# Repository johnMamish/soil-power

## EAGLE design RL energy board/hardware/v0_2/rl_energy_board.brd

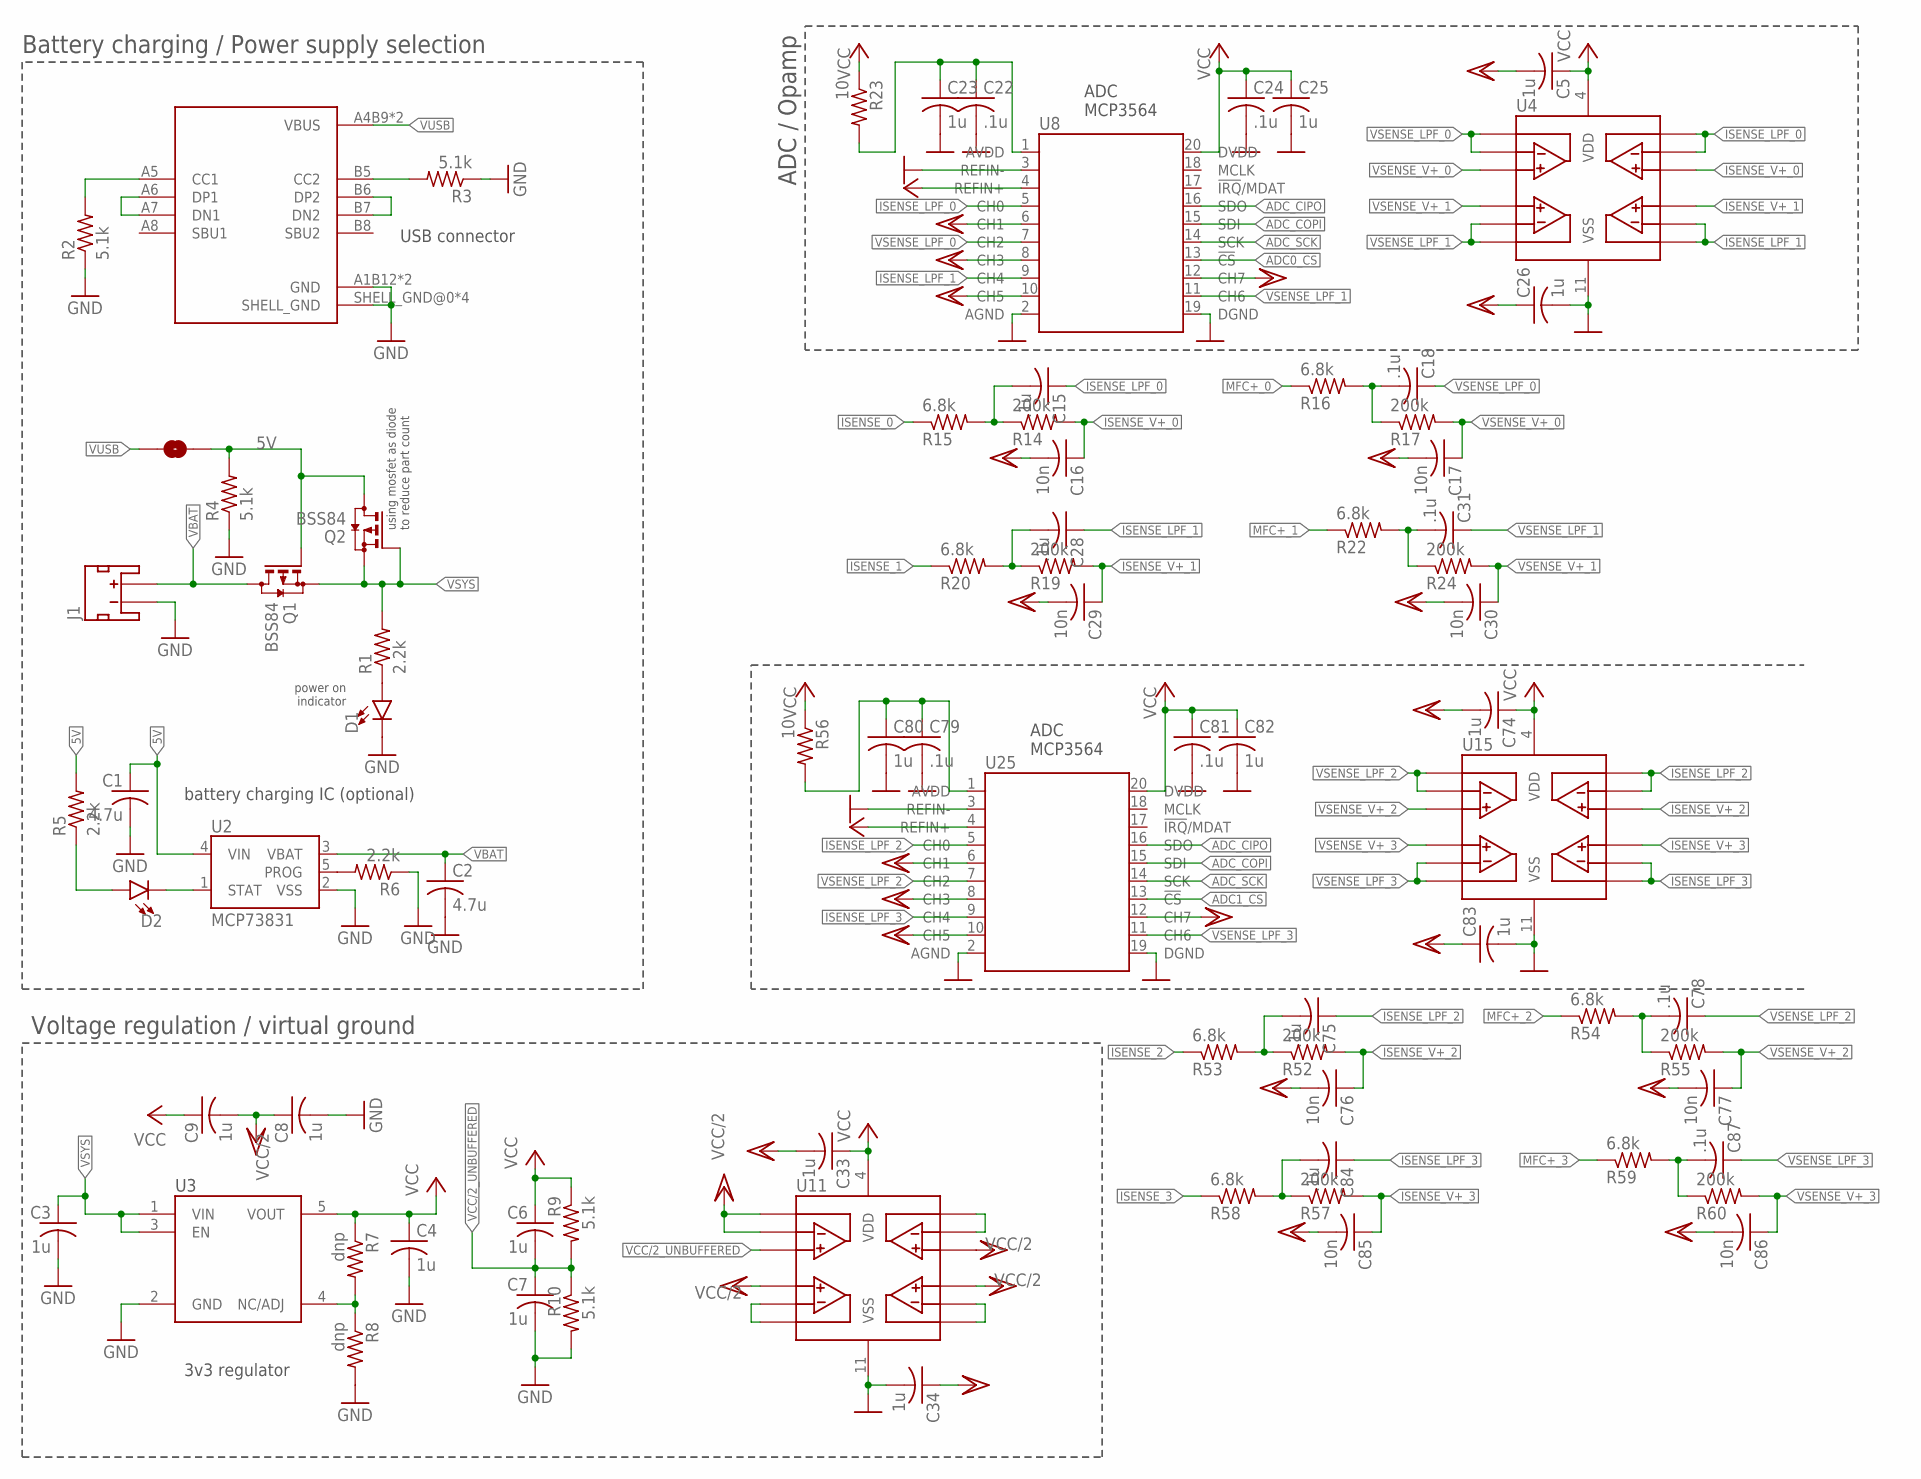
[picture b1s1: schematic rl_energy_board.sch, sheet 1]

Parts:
C1, C2: 4.7u; C0603; MFR_PN CL10A475KP8NNNC
C3, C4, C5, C6, C7, C8, C9, C23, C25, C26, C33, C34, C74, C80, C82, C83: 1u; C0402; MFR_PN CL10B105KP8NNNC
C15, C18, C22, C24, C28, C31, C75, C78, C79, C81, C84, C87: .1u; C0402; MFR_PN CL10B104KB8NNNC
C16, C17, C29, C30, C76, C77, C85, C86: 10n; C0402; MFR_PN CL10B103KB8NNNC
D1, D2: LED0603; LED-0603; MFR_PN LTST-C191KRKT
J1: JST_2MM_MALE; JST-2-SMD; MFR_PN S2B-PH-SM4-TB(LF)(SN)
J2: USB4105; MFR_PN USB4105-GF-A
JP1: JUMPER-SMT_2_NO_NO-SILK; SMT-JUMPER_2_NO_NO-SILK
Q1, Q2: BSS84; SOT23; MFR_PN BSS84W RFG
R1, R5, R6: 2.2k; R0402; MFR_PN RC0603FR-072KL
R2, R3, R4, R9, R10: 5.1k; R0402; MFR_PN RC0603FR-075K1L
R7, R8: dnp; R0402
R14, R17, R19, R24, R52, R55, R57, R60: 200k; R0402; MFR_PN RC0603FR-07200KL
R15, R16, R20, R22, R53, R54, R58, R59: 6.8k; R0402; MFR_PN RC0603FR-076K8L
R23, R56: 10; R0402; MFR_PN RNCF0603BKE4R70
U2: MCP73831; SOT23-5; MFR_PN MCP73831T-2DCI/OT
U3: AP7366; SOT95P285X130-5N; MFR_PN AP7366-33W5-7
U4, U11, U15: MCP6074; SOP65P640X120-14N; MFR_PN MCP6074T-E/ST
U8, U25: MCP3564; SOP65P640X120-20N; MFR_PN MCP3564RT-E/ST

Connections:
5V: C1.1, JP1.1, Q1.1 (G), Q2.3 (D), R4.2, R5.2, U2.4 (VIN); also elsewhere on the board
ADC0_!CS!: U8.13 (!CS); also elsewhere on the board
ADC1_!CS!: U25.13 (!CS); also elsewhere on the board
ADC_CIPO: U8.16 (SDO), U25.16 (SDO); also elsewhere on the board
ADC_COPI: U8.15 (SDI), U25.15 (SDI); also elsewhere on the board
ADC_SCK: U8.14 (SCK), U25.14 (SCK); also elsewhere on the board
GND: C1.2, C2.2, C3.2, C4.2, C7.2, C8.2, C22.2, C23.2, C24.2, C25.2, C26.2, C34.2, C79.2, C80.2, C81.2, C82.2, C83.2, D1.C, J1.1 (-), J2.A1B12 (GND), J2.B1A12 (GND), J2.SHELL_GND@0 (SHELL_GND), J2.SHELL_GND@1 (SHELL_GND), J2.SHELL_GND@2 (SHELL_GND), J2.SHELL_GND@3 (SHELL_GND), R2.1, R3.1, R4.1, R6.1, R8.2, R10.2, U2.2 (VSS), U3.2 (GND), U4.11 (VSS), U8.2 (AGND), U8.3 (REFIN-), U8.19 (DGND), U11.11 (VSS), U15.11 (VSS), U25.2 (AGND), U25.3 (REFIN-), U25.19 (DGND); also elsewhere on the board
ISENSE_0: R15.1; also elsewhere on the board
ISENSE_1: R20.1; also elsewhere on the board
ISENSE_2: R53.1; also elsewhere on the board
ISENSE_3: R58.1; also elsewhere on the board
ISENSE_LPF_0: C15.1, U4.13, U4.14, U8.5 (CH0)
ISENSE_LPF_1: C28.1, U4.8, U4.9, U8.9 (CH4)
ISENSE_LPF_2: C75.1, U15.13, U15.14, U25.5 (CH0)
ISENSE_LPF_3: C84.1, U15.8, U15.9, U25.9 (CH4)
ISENSE_V+_0: C16.1, R14.2, U4.12
ISENSE_V+_1: C29.1, R19.2, U4.10
ISENSE_V+_2: C76.1, R52.2, U15.12
ISENSE_V+_3: C85.1, R57.2, U15.10
MFC+_0: R16.1; also elsewhere on the board
MFC+_1: R22.1; also elsewhere on the board
MFC+_2: R54.1; also elsewhere on the board
MFC+_3: R59.1; also elsewhere on the board
unnamed: D1.A, R1.1
unnamed: D2.C, U2.1 (STAT)
unnamed: R6.2, U2.5 (PROG)
unnamed: J2.B6 (DP2), J2.B7 (DN2)
unnamed: J2.A6 (DP1), J2.A7 (DN1)
unnamed: J2.A5 (CC1), R2.2
unnamed: J2.B5 (CC2), R3.2
unnamed: D2.A, R5.1
unnamed: R7.2, R8.1, U3.4 (NC/ADJ)
unnamed: C28.2, R19.1, R20.2
unnamed: C22.1, C23.1, R23.2, U8.1 (AVDD)
unnamed: C15.2, R14.1, R15.2
unnamed: C18.2, R16.2, R17.1
unnamed: U11.6, U11.7
unnamed: U11.8, U11.9
unnamed: C31.2, R22.2, R24.1
unnamed: U11.13, U11.14
unnamed: C78.2, R54.2, R55.1
unnamed: C75.2, R52.1, R53.2
unnamed: C79.1, C80.1, R56.2, U25.1 (AVDD)
unnamed: C84.2, R57.1, R58.2
unnamed: C87.2, R59.2, R60.1
VBAT: C2.1, J1.2 (+), Q1.3 (D), U2.3 (VBAT)
VCC: C4.1, C5.1, C6.1, C9.1, C24.1, C25.1, C33.1, C74.1, C81.1, C82.1, R7.1, R9.1, R23.1, R56.1, U3.5 (VOUT), U4.4 (VDD), U8.4 (REFIN+), U8.20 (DVDD), U11.4 (VDD), U15.4 (VDD), U25.4 (REFIN+), U25.20 (DVDD); also elsewhere on the board
VCC/2: C5.2, C8.1, C9.2, C16.2, C17.2, C26.1, C29.2, C30.2, C33.2, C34.1, C74.2, C76.2, C77.2, C83.1, C85.2, C86.2, U8.6 (CH1), U8.8 (CH3), U8.10 (CH5), U8.12 (CH7), U11.1, U11.2, U11.5, U11.10, U11.12, U25.6 (CH1), U25.8 (CH3), U25.10 (CH5), U25.12 (CH7); also elsewhere on the board
VCC/2_UNBUFFERED: C6.2, C7.1, R9.2, R10.1, U11.3
VSENSE_LPF_0: C18.1, U4.1, U4.2, U8.7 (CH2)
VSENSE_LPF_1: C31.1, U4.6, U4.7, U8.11 (CH6)
VSENSE_LPF_2: C78.1, U15.1, U15.2, U25.7 (CH2)
VSENSE_LPF_3: C87.1, U15.6, U15.7, U25.11 (CH6)
VSENSE_V+_0: C17.1, R17.2, U4.3
VSENSE_V+_1: C30.1, R24.2, U4.5
VSENSE_V+_2: C77.1, R55.2, U15.3
VSENSE_V+_3: C86.1, R60.2, U15.5
VSYS: C3.1, Q1.2 (S), Q2.1 (G), Q2.2 (S), R1.2, U3.1 (VIN), U3.3 (EN); also elsewhere on the board
VUSB: J2.A4B9 (VBUS), J2.B4A9 (VBUS), JP1.2

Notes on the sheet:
using mosfet as diode to reduce part count
power on indicator
Battery charging / Power supply selection
Voltage regulation / virtual ground
ADC / Opamp
USB connector
battery charging IC (optional)
3v3 regulator
ADC MCP3564

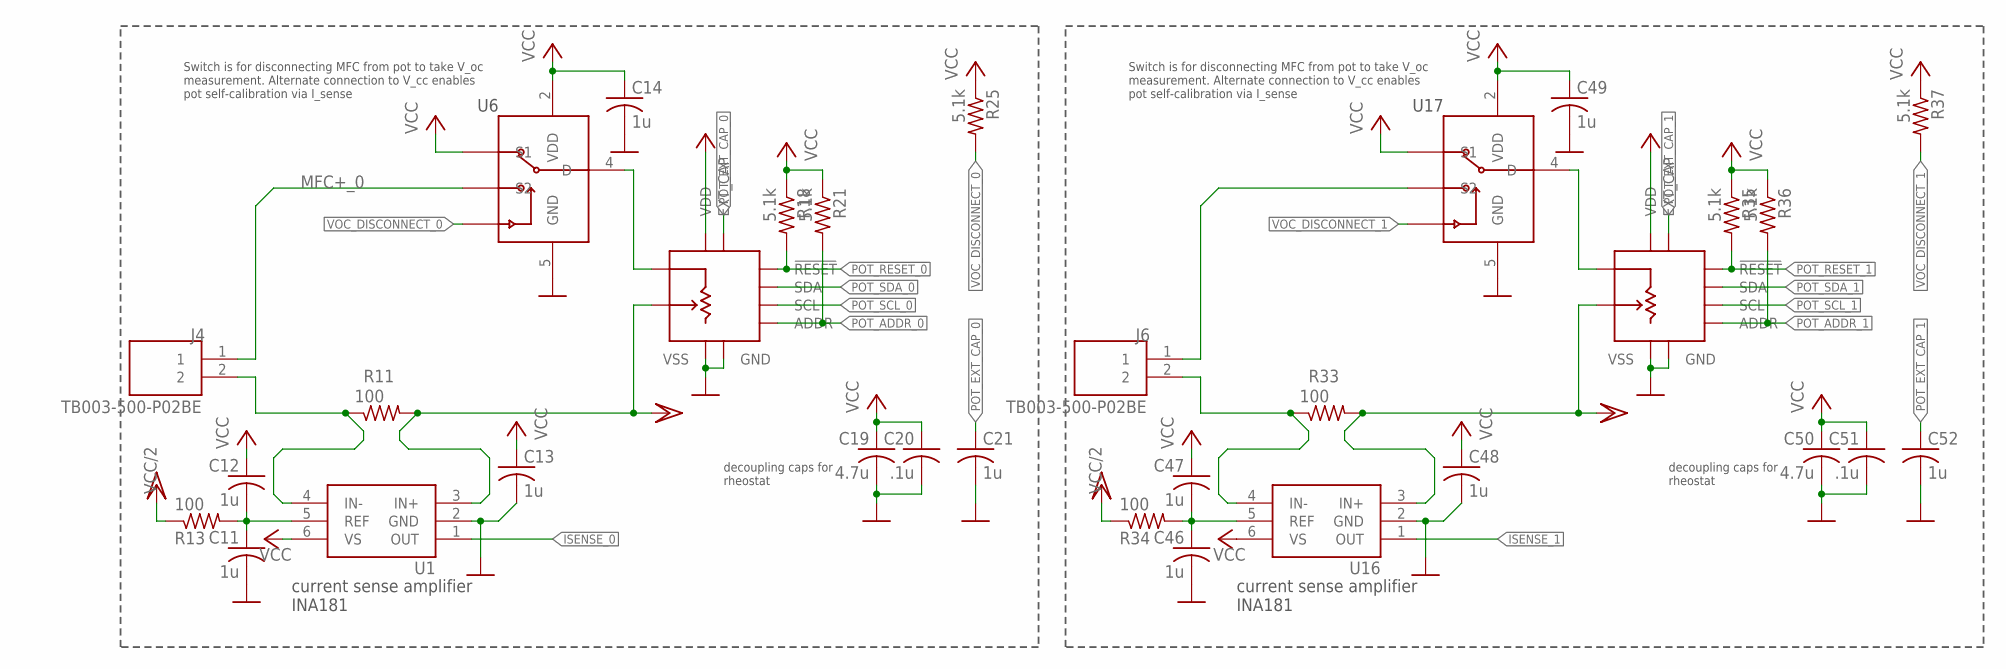
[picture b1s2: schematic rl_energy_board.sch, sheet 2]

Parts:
C11, C12, C13, C14, C21, C46, C47, C48, C49, C52: 1u; C0402; MFR_PN CL10B105KP8NNNC
C19, C50: 4.7u; C0603; MFR_PN CL10A475KP8NNNC
C20, C51: .1u; C0402; MFR_PN CL10B104KB8NNNC
J4, J6: TB003-500-P02BE; CUI_TB003-500-P02BE
R11, R33: 100; R0603; MFR_PN RNCF0603BKE4R70
R13, R34: 100; R0402; MFR_PN RT0603BRD07100RL
R18, R21, R25, R35, R36, R37: 5.1k; R0402; MFR_PN RC0603FR-075K1L
U1, U16: INA181; SOT95P280X145-6N; MFR_PN INA181A4IDBVT
U6, U17: TMUX1247; SOT65P210X110-6N; MFR_PN TMUX1247DCKR
U7, U18: AD5272BRMZ-XXX; SOP50P490X95-10N; MFR_PN AD5272BRMZ-100

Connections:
GND: C11.2, C13.2, C14.2, C19.2, C20.2, C21.2, C46.2, C48.2, C49.2, C50.2, C51.2, C52.2, U1.2 (GND), U6.5 (GND), U7.4 (VSS), U7.6 (GND), U16.2 (GND), U17.5 (GND), U18.4 (VSS), U18.6 (GND); also elsewhere on the board
ISENSE_0: U1.1 (OUT); also elsewhere on the board
ISENSE_1: U16.1 (OUT); also elsewhere on the board
MFC+_0: J4.1, U6.1 (S2); also elsewhere on the board
MFC+_1: J6.1, U17.1 (S2); also elsewhere on the board
MFC-: J4.2, R11.1, U1.4 (IN-)
MFC-_1: J6.2, R33.1, U16.4 (IN-)
unnamed: C11.1, C12.2, R13.2, U1.5 (REF)
unnamed: U6.4 (D), U7.2 (A)
unnamed: C46.1, C47.2, R34.2, U16.5 (REF)
unnamed: U17.4 (D), U18.2 (A)
POT_!RESET_0: R18.2, U7.7 (!RESET)
POT_!RESET_1: R35.2, U18.7 (!RESET)
POT_ADDR_0: R21.2, U7.10 (ADDR)
POT_ADDR_1: R36.2, U18.10 (ADDR)
POT_EXT_CAP_0: C21.1, U7.5 (EXT_CAP)
POT_EXT_CAP_1: C52.1, U18.5 (EXT_CAP)
POT_SCL_0: U7.9 (SCL); also elsewhere on the board
POT_SCL_1: U18.9 (SCL); also elsewhere on the board
POT_SDA_0: U7.8 (SDA); also elsewhere on the board
POT_SDA_1: U18.8 (SDA); also elsewhere on the board
VCC: C12.1, C13.1, C14.1, C19.1, C20.1, C47.1, C48.1, C49.1, C50.1, C51.1, R18.1, R21.1, R25.1, R35.1, R36.1, R37.1, U1.6 (VS), U6.2 (VDD), U6.3 (S1), U7.1 (VDD), U16.6 (VS), U17.2 (VDD), U17.3 (S1), U18.1 (VDD); also elsewhere on the board
VCC/2: R11.2, R13.1, R33.2, R34.1, U1.3 (IN+), U7.3 (W), U16.3 (IN+), U18.3 (W); also elsewhere on the board
VOC_DISCONNECT_0: R25.2, U6.6 (SEL); also elsewhere on the board
VOC_DISCONNECT_1: R37.2, U17.6 (SEL); also elsewhere on the board

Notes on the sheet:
Switch is for disconnecting MFC from pot to take V_oc measurement. Alternate connection to V_cc enables pot self-calibration via I_sense
current sense amplifier INA181
decoupling caps for rheostat

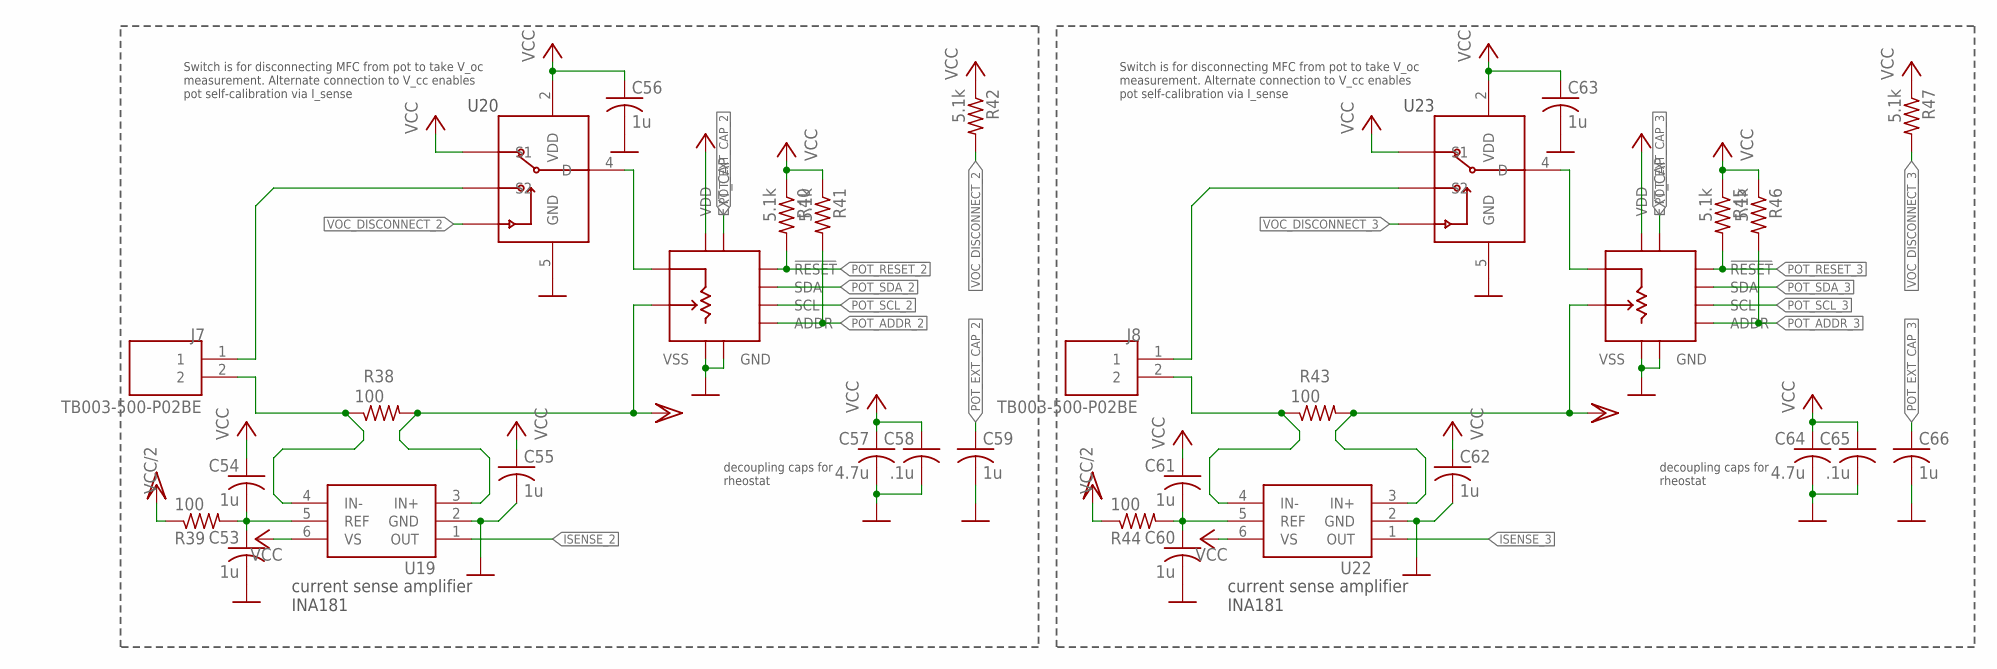
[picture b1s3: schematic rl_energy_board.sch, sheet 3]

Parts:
C53, C54, C55, C56, C59, C60, C61, C62, C63, C66: 1u; C0402; MFR_PN CL10B105KP8NNNC
C57, C64: 4.7u; C0603; MFR_PN CL10A475KP8NNNC
C58, C65: .1u; C0402; MFR_PN CL10B104KB8NNNC
J7, J8: TB003-500-P02BE; CUI_TB003-500-P02BE
R38, R43: 100; R0603; MFR_PN RNCF0603BKE4R70
R39, R44: 100; R0402; MFR_PN RT0603BRD07100RL
R40, R41, R42, R45, R46, R47: 5.1k; R0402; MFR_PN RC0603FR-075K1L
U19, U22: INA181; SOT95P280X145-6N; MFR_PN INA181A4IDBVT
U20, U23: TMUX1247; SOT65P210X110-6N; MFR_PN TMUX1247DCKR
U21, U24: AD5272BRMZ-XXX; SOP50P490X95-10N; MFR_PN AD5272BRMZ-100

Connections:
GND: C53.2, C55.2, C56.2, C57.2, C58.2, C59.2, C60.2, C62.2, C63.2, C64.2, C65.2, C66.2, U19.2 (GND), U20.5 (GND), U21.4 (VSS), U21.6 (GND), U22.2 (GND), U23.5 (GND), U24.4 (VSS), U24.6 (GND); also elsewhere on the board
ISENSE_2: U19.1 (OUT); also elsewhere on the board
ISENSE_3: U22.1 (OUT); also elsewhere on the board
MFC+_2: J7.1, U20.1 (S2); also elsewhere on the board
MFC+_3: J8.1, U23.1 (S2); also elsewhere on the board
MFC-_2: J7.2, R38.1, U19.4 (IN-)
MFC-_3: J8.2, R43.1, U22.4 (IN-)
unnamed: C53.1, C54.2, R39.2, U19.5 (REF)
unnamed: U20.4 (D), U21.2 (A)
unnamed: C60.1, C61.2, R44.2, U22.5 (REF)
unnamed: U23.4 (D), U24.2 (A)
POT_!RESET_2: R40.2, U21.7 (!RESET)
POT_!RESET_3: R45.2, U24.7 (!RESET)
POT_ADDR_2: R41.2, U21.10 (ADDR)
POT_ADDR_3: R46.2, U24.10 (ADDR)
POT_EXT_CAP_2: C59.1, U21.5 (EXT_CAP)
POT_EXT_CAP_3: C66.1, U24.5 (EXT_CAP)
POT_SCL_2: U21.9 (SCL); also elsewhere on the board
POT_SCL_3: U24.9 (SCL); also elsewhere on the board
POT_SDA_2: U21.8 (SDA); also elsewhere on the board
POT_SDA_3: U24.8 (SDA); also elsewhere on the board
VCC: C54.1, C55.1, C56.1, C57.1, C58.1, C61.1, C62.1, C63.1, C64.1, C65.1, R40.1, R41.1, R42.1, R45.1, R46.1, R47.1, U19.6 (VS), U20.2 (VDD), U20.3 (S1), U21.1 (VDD), U22.6 (VS), U23.2 (VDD), U23.3 (S1), U24.1 (VDD); also elsewhere on the board
VCC/2: R38.2, R39.1, R43.2, R44.1, U19.3 (IN+), U21.3 (W), U22.3 (IN+), U24.3 (W); also elsewhere on the board
VOC_DISCONNECT_2: R42.2, U20.6 (SEL); also elsewhere on the board
VOC_DISCONNECT_3: R47.2, U23.6 (SEL); also elsewhere on the board

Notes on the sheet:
Switch is for disconnecting MFC from pot to take V_oc measurement. Alternate connection to V_cc enables pot self-calibration via I_sense
current sense amplifier INA181
decoupling caps for rheostat

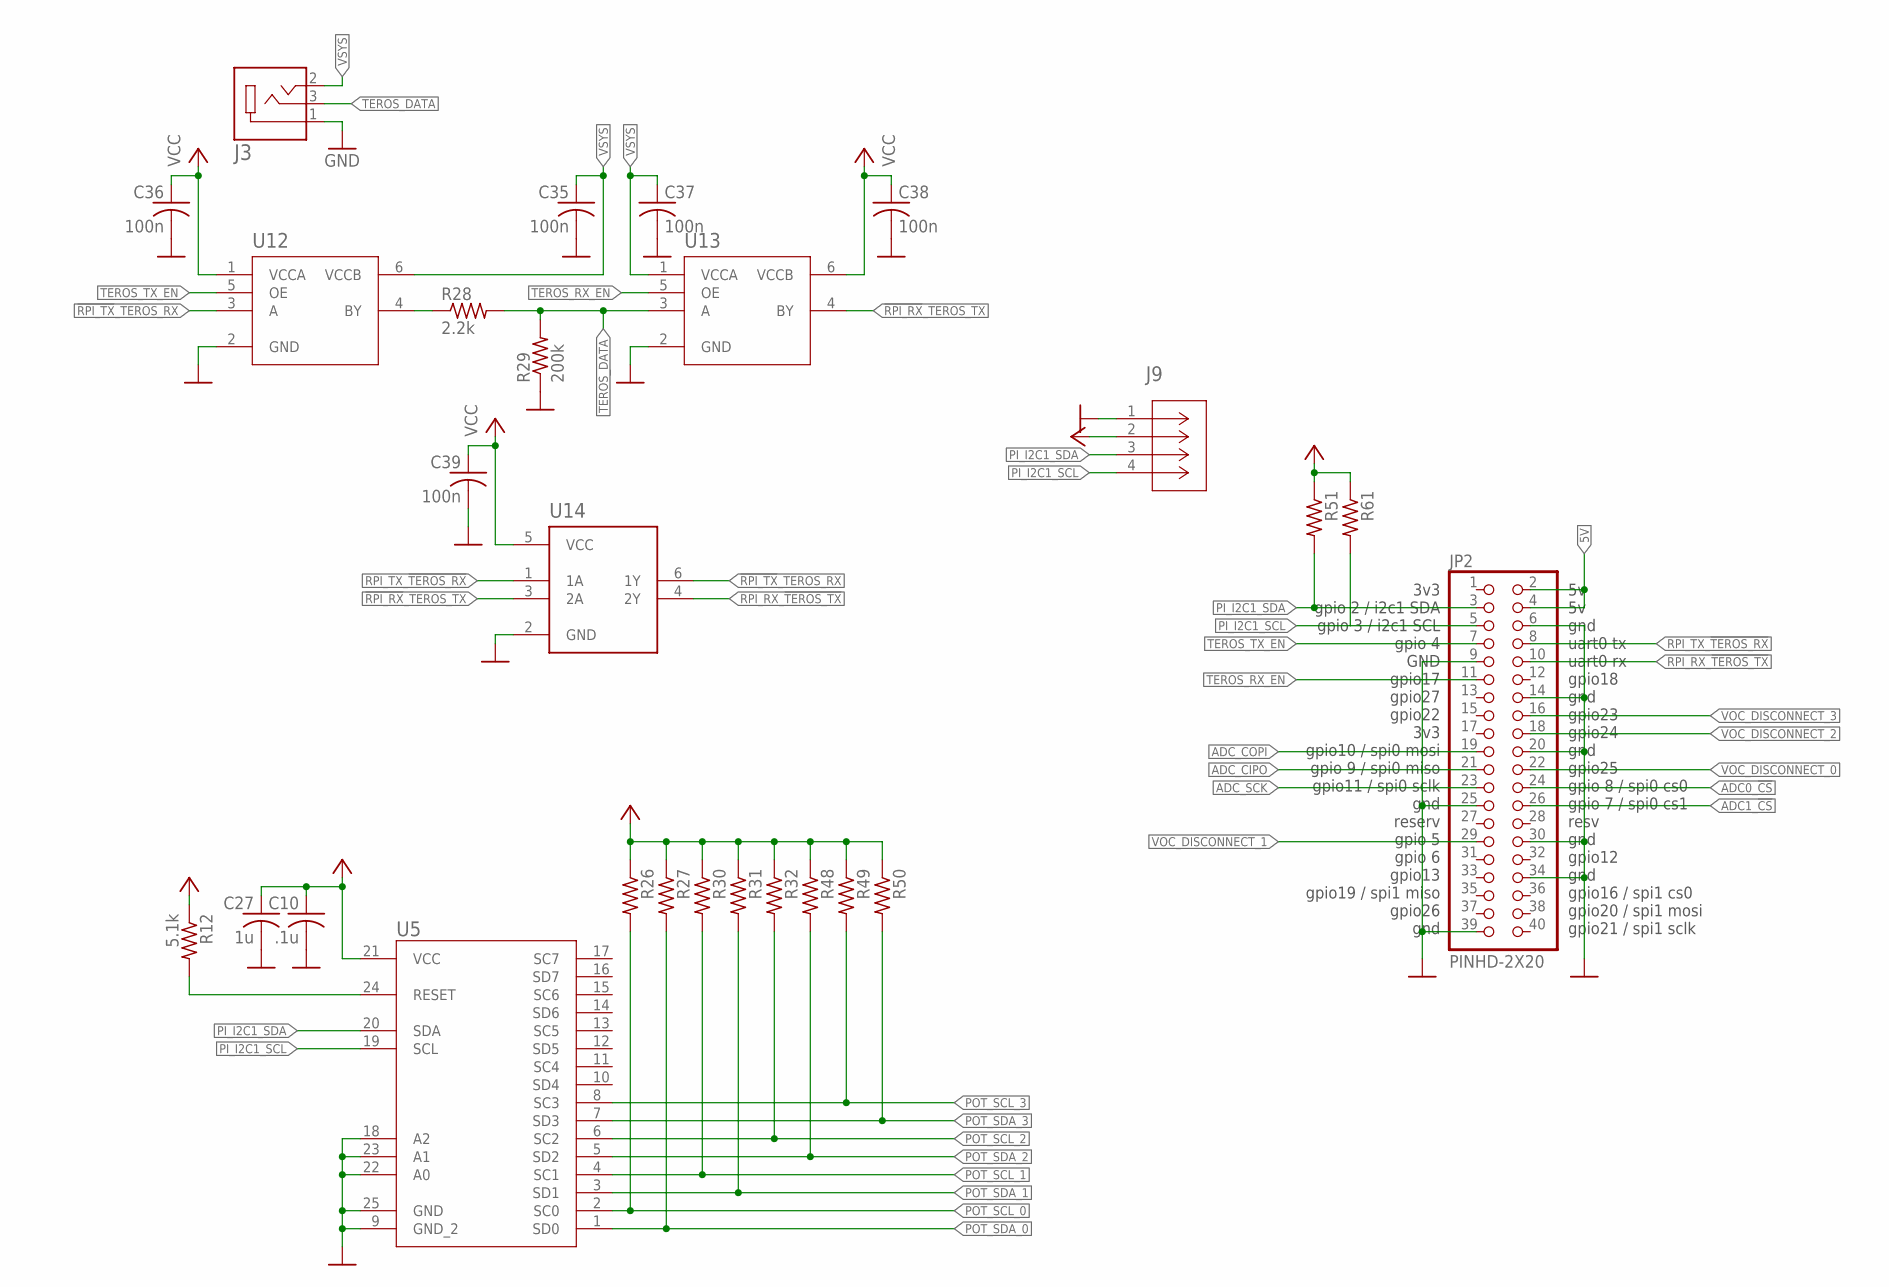
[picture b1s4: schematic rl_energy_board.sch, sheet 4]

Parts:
C10: .1u; C0402; MFR_PN CL10B104KB8NNNC
C27: 1u; C0402; MFR_PN CL10B105KP8NNNC
C35, C36, C37, C38, C39: 100n; C0402
J3: SJ-3523-SMT-TR; CUI_SJ-3523-SMT-TR
J9: SM04B-SRSS-TB; CONN_SM04B-SRSS-TB_JST
JP2: PINHD-2X20; 2X20
R12, R26, R27, R30, R31, R32, R48, R49, R50, R51, R61: 5.1k; R0402; MFR_PN RC0603FR-075K1L
R28: 2.2k; R0402
R29: 200k; R0402
U5: TCA9548ARGERQ1; QFN_GERQ1_TEX
U12, U13: TXU0101QDCKRQ1; SOT_101QDCKRQ1_TEX
U14: SN74LVC2G14DCKR; SOT65P210X110-6N

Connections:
5V: JP2.2, JP2.4; also elsewhere on the board
!RPI_RX!_TEROS_TX: U13.4 (BY), U14.3 (2A)
!RPI_TX!_TEROS_RX: U12.3 (A), U14.6 (1Y)
ADC0_!CS!: JP2.24; also elsewhere on the board
ADC1_!CS!: JP2.26; also elsewhere on the board
ADC_CIPO: JP2.21; also elsewhere on the board
ADC_COPI: JP2.19; also elsewhere on the board
ADC_SCK: JP2.23; also elsewhere on the board
GND: C10.2, C27.2, C35.2, C36.2, C37.2, C38.2, C39.2, J3.1, J9.1, JP2.6, JP2.9, JP2.14, JP2.20, JP2.25, JP2.30, JP2.34, JP2.39, R29.1, U5.9 (GND_2), U5.18 (A2), U5.22 (A0), U5.23 (A1), U5.25 (GND), U12.2 (GND), U13.2 (GND), U14.2 (GND); also elsewhere on the board
unnamed: R12.2, U5.24 (RESET)
unnamed: R28.1, U12.4 (BY)
PI_I2C1_SCL: J9.4, JP2.5, R61.2, U5.19 (SCL)
PI_I2C1_SDA: J9.3, JP2.3, R51.2, U5.20 (SDA)
POT_SCL_0: R26.2, U5.2 (SC0); also elsewhere on the board
POT_SCL_1: R30.2, U5.4 (SC1); also elsewhere on the board
POT_SCL_2: R32.2, U5.6 (SC2); also elsewhere on the board
POT_SCL_3: R49.2, U5.8 (SC3); also elsewhere on the board
POT_SDA_0: R27.2, U5.1 (SD0); also elsewhere on the board
POT_SDA_1: R31.2, U5.3 (SD1); also elsewhere on the board
POT_SDA_2: R48.2, U5.5 (SD2); also elsewhere on the board
POT_SDA_3: R50.2, U5.7 (SD3); also elsewhere on the board
RPI_RX_!TEROS_TX!: JP2.10, U14.4 (2Y)
RPI_TX_!TEROS_RX!: JP2.8, U14.1 (1A)
TEROS_DATA: J3.3, R28.2, R29.2, U13.3 (A)
TEROS_RX_EN: JP2.11, U13.5 (OE)
TEROS_TX_EN: JP2.7, U12.5 (OE)
VCC: C10.1, C27.1, C36.1, C38.1, C39.1, J9.2, R12.1, R26.1, R27.1, R30.1, R31.1, R32.1, R48.1, R49.1, R50.1, R51.1, R61.1, U5.21 (VCC), U12.1 (VCCA), U13.6 (VCCB), U14.5 (VCC); also elsewhere on the board
VOC_DISCONNECT_0: JP2.22; also elsewhere on the board
VOC_DISCONNECT_1: JP2.29; also elsewhere on the board
VOC_DISCONNECT_2: JP2.18; also elsewhere on the board
VOC_DISCONNECT_3: JP2.16; also elsewhere on the board
VSYS: C35.1, C37.1, J3.2, U12.6 (VCCB), U13.1 (VCCA); also elsewhere on the board

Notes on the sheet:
3v3 gpio 2 / i2c1 SDA gpio 3 / i2c1 SCL gpio 4 GND gpio17 gpio27 gpio22 3v3 gpio10 / spi0 mosi gpio 9 / spi0 miso gpio11 / spi0 sclk gnd reserv gpio 5 gpio 6 gpio13 gpio19 / spi1 miso gpio26 gnd
5v 5v gnd uart0 tx uart0 rx gpio18 gnd gpio23 gpio24 gnd gpio25 gpio 8 / spi0 cs0 gpio 7 / spi0 cs1 resv gnd gpio12 gnd gpio16 / spi1 cs0 gpio20 / spi1 mosi gpio21 / spi1 sclk

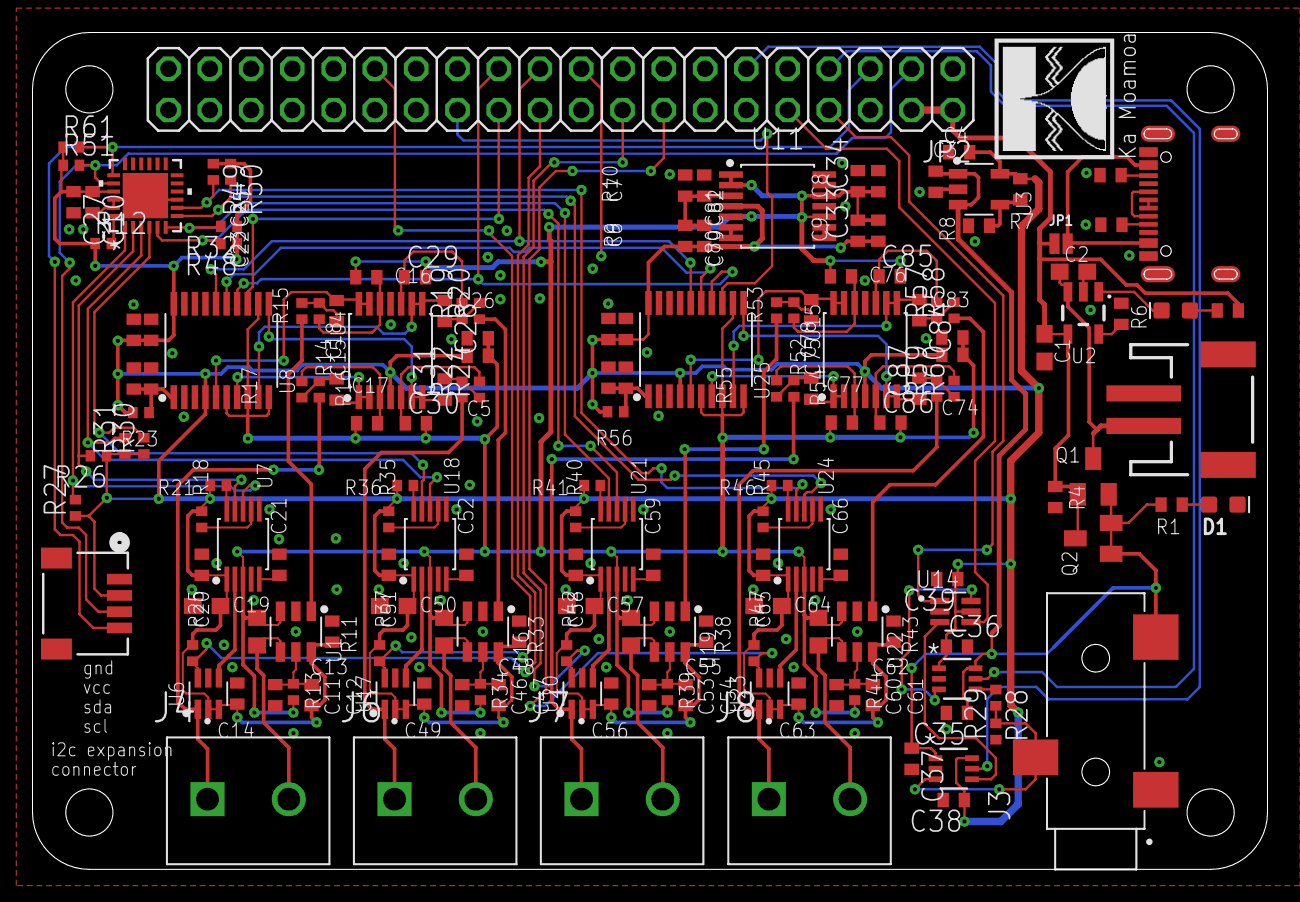
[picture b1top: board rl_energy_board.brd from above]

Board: 2 copper layers, 76.0 x 51.5 mm, 171 parts (0 on the bottom side), 106 nets.

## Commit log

2023-01-28 initial RL board design wip
2024-02-15 add raspberry pi README and existing raspberry pi software
2024-02-15 ADC passes smoke test; need to validate current measurements still and quantify ADC accuracy / precision.
2024-02-15 add gaincal settings to ADC; performance now accurate to ~1mV
2024-04-01 split some code out of soil_power.py
2024-04-01 attribution: Divyaansh Singh; break more code out of soil_power.py
2024-04-10 add some utilities to help collect data
2024-04-20 logging_values
2024-04-20 Update log_v_i_readings.py
    Logging values with cleanup GIPO
2024-04-20 test_outputs
2024-07-01 Add logging framework
2024-07-09 fixed issue - added adc calib fix + restored original vref constant
2024-08-06 PCB rev almost ready
2024-09-03 adding dockerfile
2024-09-03 added config templating + k8s working
2024-10-22 updates from rpi
2024-10-22 update 2's complement
2024-10-22 changed endiannes in mcp
2025-04-21 add adc chip select
2025-04-21 remove numpy version requirement
2025-04-21 fix files syntax
2025-05-22 final pcb
2025-05-23 update spi code

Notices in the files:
parts and their libraries:
SparkFun-Connectors: Licensing: Creative Commons ShareAlike 4.0 International - https://creativecommons.org/licenses/by-sa/4.0
COPYRIGHT: Copyright (C) 2024 Ultra Librarian. All rights reserved.
